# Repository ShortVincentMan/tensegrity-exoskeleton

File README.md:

# Feedback Control of an Upper-Limb Tensegrity Exoskeleton

Research by **Vincent Le**, advised by **Dr. Alan Zhang**, Department of Mechanical Engineering, Cal Poly San Luis Obispo. Built during the **2026 Summer Undergraduate Research Program (SURP)**.

Most upper-limb exoskeletons make you pick a tradeoff: rigid frames are heavy and restrictive, and cable systems usually need a big external frame or a bulky pack of motors and batteries. I wanted to see if a tensegrity structure (rods held together by cables and springs, closer to how bones and muscles actually work) could give real elbow assistance while staying light and compliant.

Over about 40 lab days I took an inherited tensegrity arm, rebuilt it to actually fit on a person, and turned it into a working electromechanical system: two stepper-driven cable spools on the shoulder, two BNO085 IMUs on the upper arm and forearm, an ESP32 running a 100 Hz state machine, and a custom PCB I designed in KiCad and had fabricated.

**What works:** both IMUs stream reliably, the firmware turns them into an elbow angle, and the motors follow the arm and trigger an assist when the arm stalls mid-curl. **What doesn't (yet):** the motors are too weak. With a 5 lb dumbbell the system stalled, and test participants didn't feel meaningful lifting help. This is a proof of concept for the sensing and control loop, not a finished assistive device.

### Start here (2-minute tour)

| If you want to see... | Look at |
| --- | --- |
| The control logic | [`firmware/controller/src/controller.cpp`](firmware/controller/src/controller.cpp): the follow / assist / release state machine |
| IMU packet parsing and elbow-angle math | [`firmware/controller/lib/exo_core`](firmware/controller/lib/exo_core/src) |
| The unit tests | [`firmware/controller/test`](firmware/controller/test) |
| The PCB | [`hardware/electronics/pcb-v1`](hardware/electronics/pcb-v1) (KiCad + Gerbers for the fabricated Rev A board) and the [layout image](results/figures/photos/pcb-layout.png) |
| How it all came together | [Build log](docs/build-log.md) |
| The research poster | [Poster](results/poster/source-and-previews/finalposter.jpg) |

## What I built

| Area | Details |
| --- | --- |
| **Mechanical** | Redesigned the tensegrity arm around my own arm, then designed and printed the parts: spools, fairleads, motor and IMU mounts, an electronics enclosure, and many iterations of rod caps. I swapped about 40 elastic cables for tuned string-and-spring pairs and added a shoulder harness so it can be worn. |
| **Sensing** | Two BNO085 IMUs in UART-RVC mode, each on its own ESP32 UART. The firmware validates every 19-byte packet with a checksum, converts each IMU to a quaternion, and takes the relative rotation as the elbow angle. |
| **Control** | A 100 Hz state machine (disabled, calibrating, follow, assist, release, fault). In follow, the spools keep the cables just slack as the arm moves. If the arm dips while held up (a stall), it switches to assist and winds the cable, then releases when motion resumes, the arm is lowered, or a time limit is hit. Includes filtering, a deadband, travel limits, sensor-loss shutdown, and a manual stop switch. |
| **Electronics** | Prototyped on a breadboard, then a perfboard, then designed a 2-layer PCB (Rev A, fabricated through OSH Park): socketed ESP32 and A4988 stepper drivers, JST-XH connectors for the IMUs and motors, a Mini360 buck converter, an optional XT30 LiPo input, sized power traces, and an antenna keep-out. ERC and DRC clean. |
| **Testing** | Dual-IMU angle validation on my arm and a rigid dummy arm, spool and cable-travel measurement, six IMU controller trials, and an EMG pilot comparing lifts with and without the exoskeleton. |

### Problems I had to solve

- **I2C kept failing on the IMUs.** After a full day of isolating hardware, swapping boards and checking every connection with a multimeter, the clone IMU boards just wouldn't stay on the I2C bus. I switched both IMUs to UART-RVC on separate ESP32 ports, wrote a packet decoder, and both have streamed reliably since. Independent channels also mean one bad sensor can't take down the bus.
- **The perfboard broke.** The ESP32's USB connector snapped off, and with everything soldered down it wasn't worth repairing. That's what pushed me to design the PCB with socketed, swappable parts.
- **The angle reads low at large flexion.** Validation showed it's accurate up to about 45° but underestimates by roughly 17 to 20° near 90 to 120°. The controller is calibrated against that (a measured 83° corresponds to a physical 100°), and fixing it properly is on the next-steps list.
- **The motors are underpowered.** Each spool gives about 56.5 mm of cable per revolution and needs 200 to 220 mm to go from 0 to 100°. The steppers can do that, but they can't hold a real load. The next revision needs more torque.

## Key results

**Elbow angle validation** (100 samples per point, neutral-relative quaternion method):

| Actual angle | Measured, worn on arm | Measured, rigid dummy arm |
| ---: | ---: | ---: |
| ~0° | 1.6° | 0.7° |
| ~45° | 33.2° | 44.6° |
| ~90° | 75.7° | 72.7° |
| ~120° | 99.7° | 101.2° |
| back to ~0° | 10.9° | 19.7° |

Readings rise consistently with flexion, which is good enough for feedback control, but the return-to-zero offset and the high-angle underestimate still need work.

**Motion trials:** six recorded controller trials show the IMUs tracking motion and the controller switching into assist. Participants didn't notice real lifting help. The EMG pilot wasn't clean enough (timing drift, uneven recording intervals) to say whether muscle effort went down. Details are in [limitations](results/limitations.md).

## Build photos

| Worn prototype | Electronics enclosure | PCB layout (KiCad) |
| --- | --- | --- |
|  |  |  |

| Tensegrity frame | CAD assembly |
| --- | --- |
|  |  |

## Repo layout

| Folder | What's in it |
| --- | --- |
| [`firmware/`](firmware/README.md) | ESP32 firmware (PlatformIO): the main controller, trial loggers, and a dual-IMU test |
| [`hardware/`](hardware/README.md) | My CAD parts, the spring calculator, and the KiCad PCB |
| [`experiments/`](experiments/imu-controller-demo/README.md) | Data from the six IMU controller trials |
| [`analysis/`](analysis/README.md) | Python for the IMU trials, MATLAB for the EMG pilot |
| [`results/`](results/README.md) | Figures, the poster, and [limitations](results/limitations.md) |
| `docs/` | [Build log](docs/build-log.md), [wiring](docs/wiring.md), [methods](docs/methods.md), and the [research question](docs/research-question.md) |

The raw EMG recordings aren't published here, but the code that processed them is.

## Running it

**Firmware** (needs [PlatformIO](https://platformio.org/)):

```sh
pio run -d firmware/controller            # build
pio run -d firmware/controller -t upload  # flash an ESP32
```

Wiring is in [docs/wiring.md](docs/wiring.md).

**Unit tests** run on your computer, no ESP32 needed:

```sh
pio test -d firmware/controller -e native
```

They cover the IMU packet parser (checksums, resyncing after garbage bytes), the quaternion elbow-angle math, and the stall detection that decides when to assist. GitHub Actions runs them and builds the ESP32 firmware on every push.

**IMU analysis** (Python 3):

```sh
python -m venv .venv && source .venv/bin/activate
pip install -r analysis/requirements.txt
python analysis/imu/analyze_imu.py --output analysis/reproduced/imu
```

This regenerates the trial summaries and plots from the raw CSVs.

## Next steps

If I keep going, the priorities are stronger actuation (higher-torque motors and better cable pretension), a load cell to measure actual cable force, a better angle calibration, and recording IMU and EMG together with a standard movement protocol.

## Thanks

Thanks to Dr. Alan Zhang for advising me, to Israel Villegas, whose earlier tensegrity arm was my starting point, and to Robert, who helped me assemble and debug the Rev A board. Tom Flemons' tensegrity arm models were a big influence on the structure.

Shared with my advisor's approval. Everything in `hardware/` is my own design; inherited and vendor CAD is left out.

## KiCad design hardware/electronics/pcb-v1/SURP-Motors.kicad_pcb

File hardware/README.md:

# Hardware

Everything here is my own design. The original tensegrity arm I started from, and any vendor CAD, isn't included.

## Mechanical

`mechanical/components/` has the 3D-printed parts, grouped by function. Each folder keeps the iterations, because most parts took several tries to print, fit, and survive being worn. `.f3d` files are Fusion 360 sources, and `.stl`/`.3mf` files are ready to print.

Latest version of each part:

| Part | File |
| --- | --- |
| Electronics housing and lid | `enclosure/my own cad/refined housing.stl`, `reifned lid.stl` (Fusion source: `electronics housing.f3d`) |
| Fairlead and cap | `fairleads/my own cad/new fairlead.stl` (source: `new fairlead.f3d`), `revised Fairlead Cap.stl` |
| Spool for the SY20STH30 motor | `spools/my own cad/v2 sy20sth30-0604a motor cap.stl` |
| Spool for the 11HS18 motor | `spools/my own cad/tolerant spool 11hs18-0674s motor cap.stl` |
| Motor mount | `motor-mounts/my own cad/new motor plate.stl` |
| IMU mount | `imu-mounts/my own cad/wider imu plate.stl` |
| Node connector | `connectors-and-caps/my own cad/New Aluminum Connector.stl` |

`mechanical/calculations/Tensegrity_Cable_and_Spring_Calculator.xlsx` is the spreadsheet I used to size the springs and string lengths for each cable.

## Electronics

| Folder | What it is |
| --- | --- |
| `electronics/pcb-v1/` | **Rev A, the board I had fabricated (OSH Park).** KiCad project, plus Gerbers and drill files in `fabrication/`. |
| `electronics/pcb-v2/` | A follow-up revision. Designed but not fabricated or tested. |

Rev A design notes:

- The ESP32 and both A4988 drivers sit in female headers, so a dead part can be swapped without desoldering. (A snapped USB connector on the old perfboard is why.)
- JST-XH connectors for the IMUs and motors.
- Motor power is routed separately from logic. A Mini360 buck converter feeds 5 V from the battery, and there's an optional XT30 LiPo input.
- Trace widths are 0.5 mm for logic, 1 mm for motor power, and 1.5 mm for the XT30 input. There's a copper keep-out under the ESP32 antenna.

If KiCad complains about missing footprints when you open the project, some came from downloaded libraries that aren't bundled here. The pin map is in [docs/wiring.md](../docs/wiring.md).

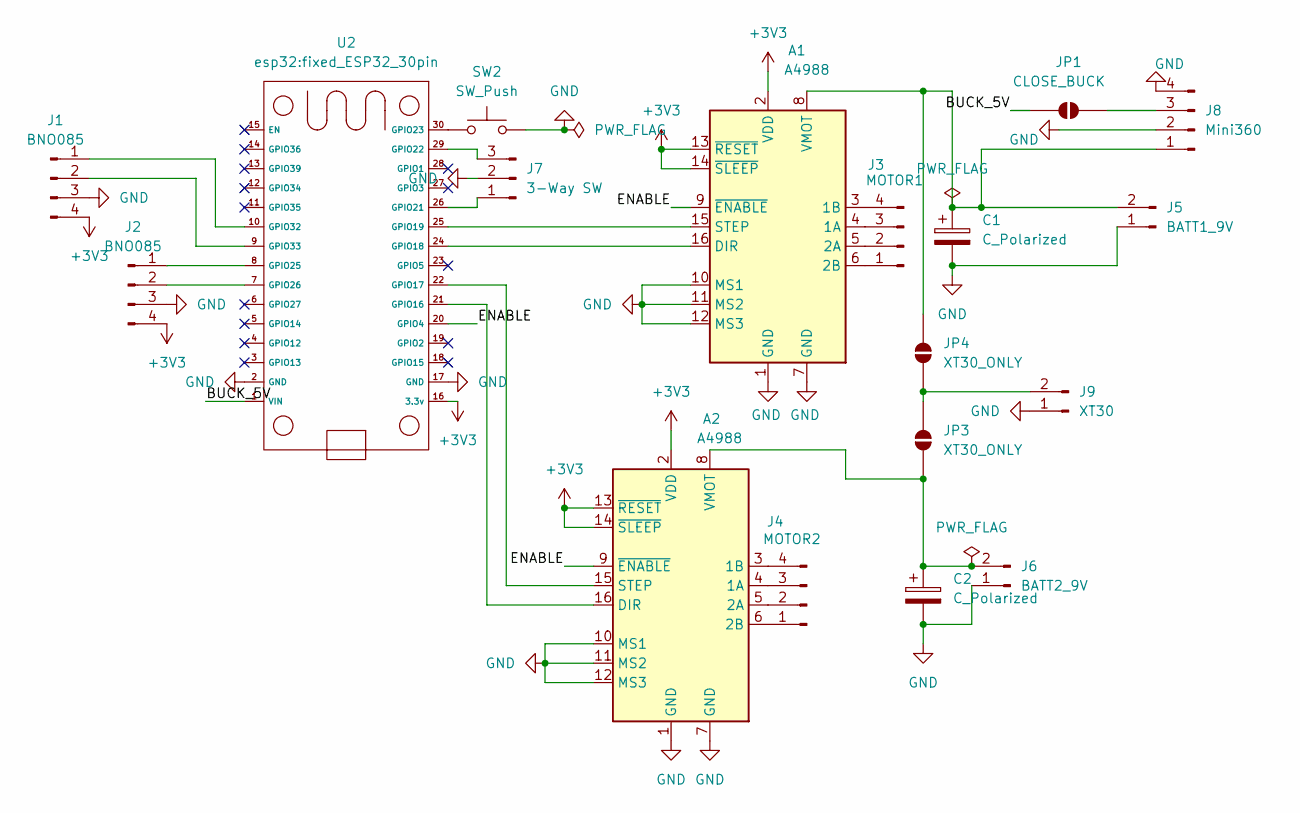
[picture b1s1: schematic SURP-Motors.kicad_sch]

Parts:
A1, A2: A4988; Pololu_Breakout-16_15.2x20.3mm
C1, C2: C_Polarized; CP_Radial_D6.3mm_P2.50mm
J1, J2: BNO085; JST_EH_S4B-EH_1x04_P2.50mm_Horizontal
J3: MOTOR1; JST_EH_B4B-EH-A_1x04_P2.50mm_Vertical
J4: MOTOR2; JST_EH_B4B-EH-A_1x04_P2.50mm_Vertical
J5: BATT1_9V; JST_EH_S2B-EH_1x02_P2.50mm_Horizontal
J6: BATT2_9V; JST_EH_S2B-EH_1x02_P2.50mm_Horizontal
J7: 3-Way SW; JST_EH_B3B-EH-A_1x03_P2.50mm_Vertical
J8: Mini360; Mini360_step-down
J9: XT30; AMASS_XT30U-M_1x02_P5.0mm_Vertical
JP1: CLOSE_BUCK; SolderJumper-2_P1.3mm_Open_RoundedPad1.0x1.5mm
JP3, JP4: XT30_ONLY; SolderJumper-2_P1.3mm_Open_RoundedPad1.0x1.5mm
SW2: SW_Push; SW_SPST_PTS645Sx43SMTR92
U2: fixed_ESP32_30pin

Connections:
+3V3: A1.2 (VDD), A1.13 (~RESET), A1.14 (~SLEEP), A2.2 (VDD), A2.13 (~RESET), A2.14 (~SLEEP), J1.4, J2.4, U2.16 (3.3v)
/BUCK_5V: JP1.1 (A), U2.1 (VIN)
/ENABLE: A1.9 (~ENABLE), A2.9 (~ENABLE), U2.20 (GPIO4)
GND: A1.1 (GND), A1.7 (GND), A1.10 (MS1), A1.11 (MS2), A1.12 (MS3), A2.1 (GND), A2.7 (GND), A2.10 (MS1), A2.11 (MS2), A2.12 (MS3), C1.2, C2.2, J1.3, J2.3, J5.1, J6.1, J7.2, J8.2, J8.4, J9.1, SW2.2, U2.2 (GND), U2.17 (GND)
unnamed: A1.4 (1A), J3.3
unnamed: A1.3 (1B), J3.4
unnamed: A1.5 (2A), J3.2
unnamed: A1.6 (2B), J3.1
unnamed: A1.16 (DIR), U2.24 (GPIO18)
unnamed: A1.15 (STEP), U2.25 (GPIO19)
unnamed: A1.8 (VMOT), C1.1, J5.2, J8.1, JP4.2 (B)
unnamed: A2.4 (1A), J4.3
unnamed: A2.3 (1B), J4.4
unnamed: A2.5 (2A), J4.2
unnamed: A2.6 (2B), J4.1
unnamed: A2.16 (DIR), U2.21 (GPIO16)
unnamed: A2.15 (STEP), U2.22 (GPIO17)
unnamed: A2.8 (VMOT), C2.1, J6.2, JP3.2 (B)
unnamed: J1.1, U2.10 (GPIO32)
unnamed: J1.2, U2.9 (GPIO33)
unnamed: J2.1, U2.8 (GPIO25)
unnamed: J2.2, U2.7 (GPIO26)
unnamed: J7.1, U2.26 (GPIO21)
unnamed: J7.3, U2.29 (GPIO22)
unnamed: J8.3, JP1.2 (B)
unnamed: J9.2, JP3.1 (A), JP4.1 (A)
unnamed: SW2.1, U2.30 (GPIO23)

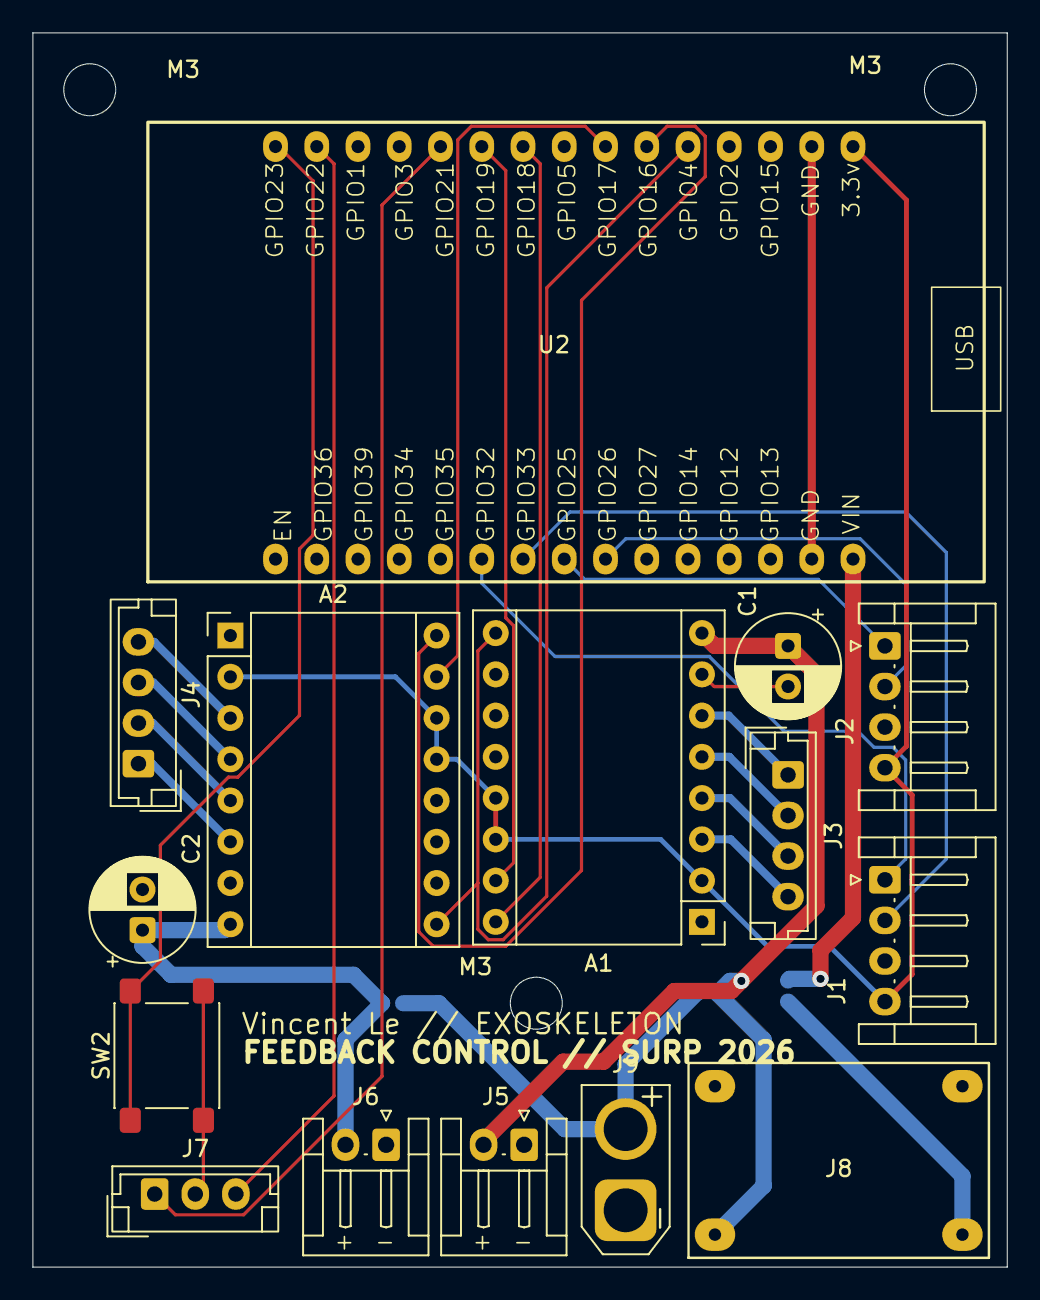
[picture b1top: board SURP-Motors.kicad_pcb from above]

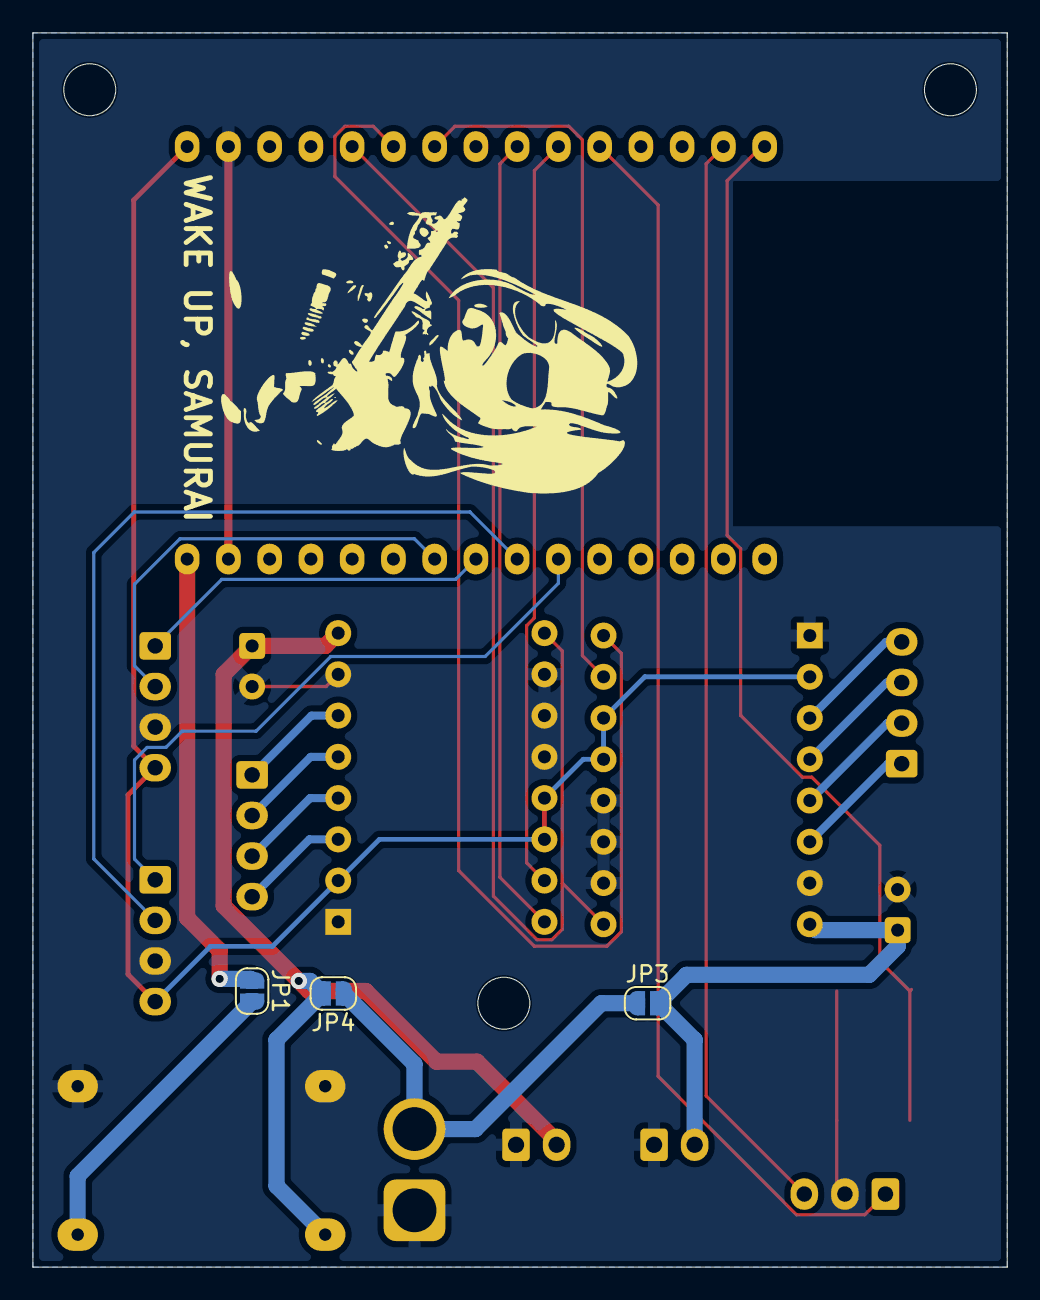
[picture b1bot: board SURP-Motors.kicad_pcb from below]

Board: 2 copper layers, 60.0 x 76.0 mm, 21 parts (3 on the bottom side), 27 nets.

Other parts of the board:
M3, M3#2, M3#3: MountingHole_3.2mm_M3
